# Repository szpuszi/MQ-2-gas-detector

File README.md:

# MQ-2 Gas Detector V1.0
It's my first custom PCB project created as part of the Hack Club Fallout.
It is designed to detect gas leaks and potential fire hazards.
This project also contains a case.

I made this because I wanted to practice making PCBs and create a practical safety device.
I use it by letting it sit and monitor gas levels in my room to ensure I'm in a safe environment.

## How it works:
The heart of this project is ATmega328P microcontroller. The board is powered via 5V USB-C (Adafruit 4090). The firmware features pre-heating phase (5mins) and a startup test function which lights up the LEDs and beeps the buzzer so you can know if it works correctly. It monitors gas levels in the air using an MQ-2 sensor and indicates safety levels by 3 LEDs and a buzzer:
- 🟢 Air is safe.
- 🟡 Gas levels are elevated. (warning)
- 🔴 High gas levels, it may be unsafe to inhale them.
<small> Thresholds were calibrated based on local home testing, sensitivity can vary depending on environment and gas type. </small>

### Shopping list 🛒: 
<small> BOM is available [here](Manufacturing/BOM.csv) </small>
You will also need:
- basic soldering kit (soldering iron, solder)
- PCB (can order on websites like JLCPCB, files for them are in Manufacturing Files.zip folder)
- Double Sided Tape
- DuPont Male/Female wires
- Glue (for the case, it needs to stick to plastic)
- cutting pliers

Total for everything is ≈ 40USD

### Manufacturing Notes🏭:
<small> All files required for production are included [here](Manufacturing/Manufacturing%20Files.zip) </small>

## 📖 Fallout Zine Page

# Assembly and firmware
Refer to the schematic and PCB layout for assembly. The PCB features a well detailed silkscreen with all components values and identifiers clearly marked to ensure easy and error-free assembly. The firmware is available [here](firmware/gas_detector.ino)
# Gallery📷
**CASE**

**PCB**

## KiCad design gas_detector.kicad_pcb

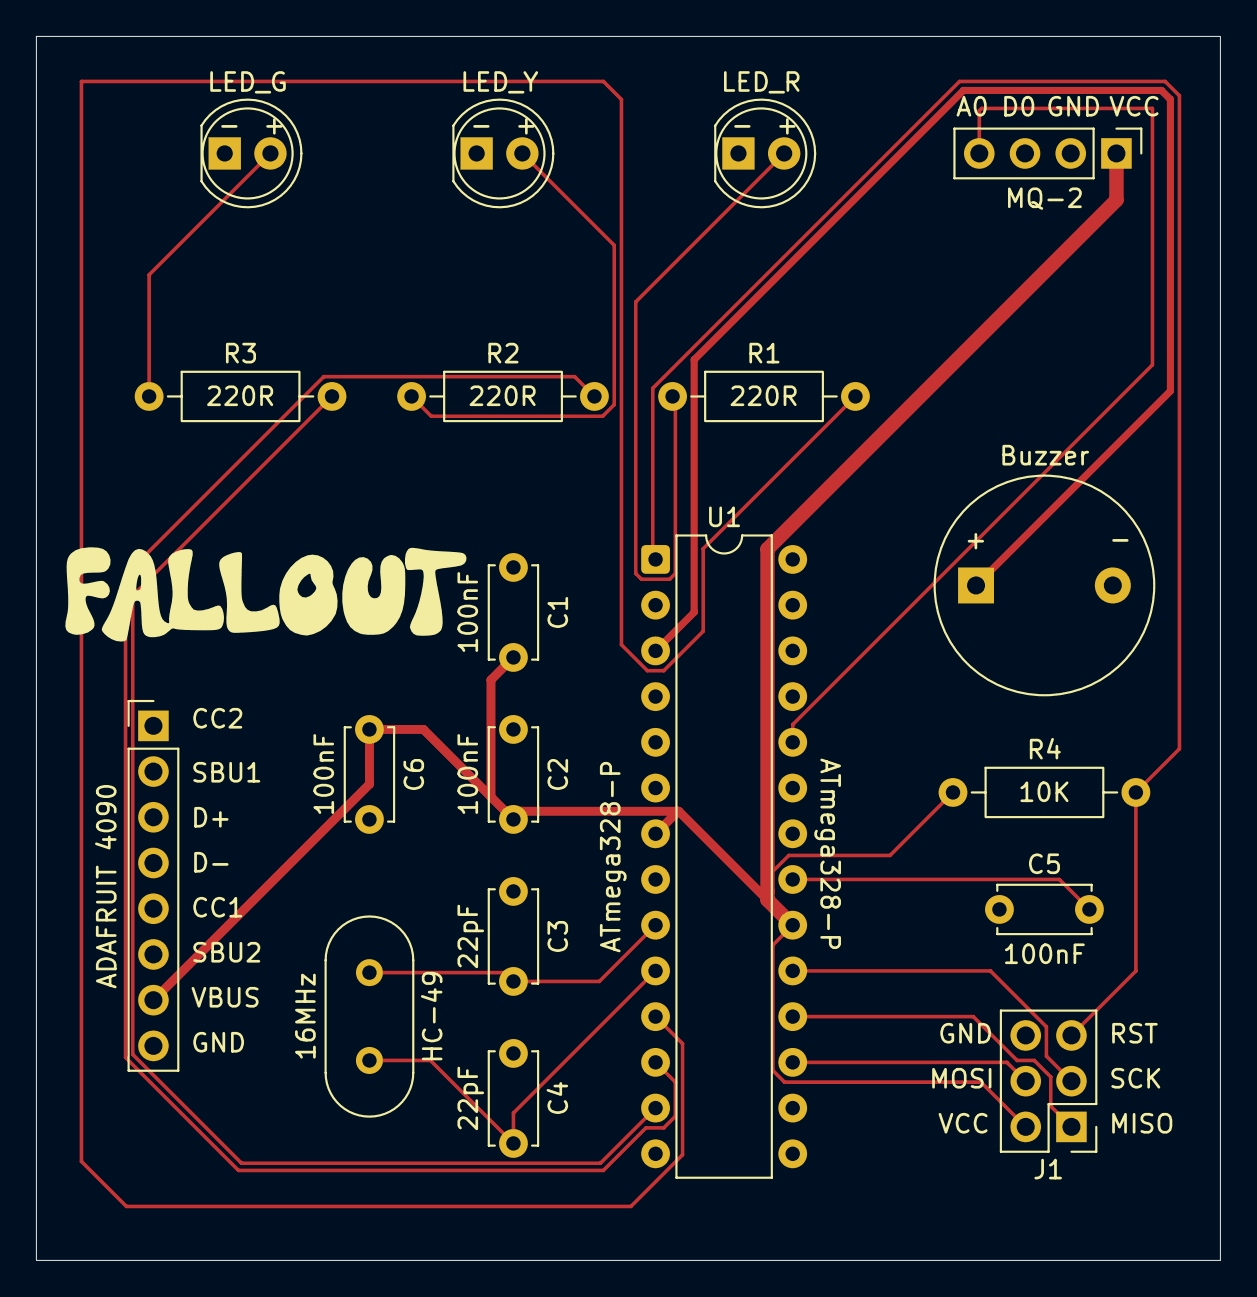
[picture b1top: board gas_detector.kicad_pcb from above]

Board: 2 copper layers, 65.8 x 68.0 mm, 19 parts (0 on the bottom side), 17 nets.

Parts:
Buzzer: Buzzer; Buzzer_12x9.5RM7.6
C1, C2, C5, C6: 100nF; C_Disc_D5.0mm_W2.5mm_P5.00mm
C3, C4: 22pF; C_Disc_D5.0mm_W2.5mm_P5.00mm
HC-49: 16MHz; Crystal_HC49-U_Vertical
J1: ISP; PinHeader_2x03_P2.54mm_Vertical
J2: Conn_01x08; PinHeader_1x08_P2.54mm_Vertical
LED_G: LED_G; LED_D5.0mm
LED_R: LED_R; LED_D5.0mm
LED_Y: LED_Y; LED_D5.0mm
MQ-2: MQ-2; PinHeader_1x04_P2.54mm_Vertical
R1, R2, R3: 220R; R_Axial_DIN0207_L6.3mm_D2.5mm_P10.16mm_Horizontal
R4: 10K; R_Axial_DIN0207_L6.3mm_D2.5mm_P10.16mm_Horizontal
U1: ATmega328P-P; DIP-28_W7.62mm

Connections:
GND: Buzzer.2 (-), C1.1, C2.1, C3.1, C4.1, C5.1, C6.1, J1.6 (GND), J2.8 (GND), LED_G.1 (K), LED_R.1 (K), LED_Y.1 (K), MQ-2.2 (GND), U1.8 (GND), U1.22 (GND)
unnamed: Buzzer.1 (+), U1.3 (PD1)
unnamed: LED_G.2 (A), R3.1
unnamed: LED_Y.2 (A), R2.1
unnamed: LED_R.2 (A), R1.1
unnamed: J1.1 (MISO), U1.18 (PB4)
unnamed: J1.4 (MOSI), U1.17 (PB3)
unnamed: J1.5 (RST), R4.2, U1.1 (~RESET/PC6)
unnamed: J1.3 (SCK), U1.19 (PB5)
unnamed: MQ-2.4 (A0), U1.24 (PC1)
unnamed: C5.2, U1.21 (AREF)
unnamed: R1.2, U1.11 (PD5)
unnamed: R2.2, U1.12 (PD6)
unnamed: R3.2, U1.13 (PD7)
unnamed: C3.2, HC-49.1, U1.9 (XTAL1/PB6)
unnamed: C4.2, HC-49.2, U1.10 (XTAL2/PB7)
VCC: C1.2, C2.2, C6.2, J1.2 (VCC), J2.7 (VBUS), MQ-2.1 (VCC), R4.1, U1.7 (VCC), U1.20 (AVCC)

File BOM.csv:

Designator,Value,Quantity,Description,Link
U1,ATmega328P-P,1,Microcontroller (DIP-28),https://www.digikey.com/en/products/detail/microchip-technol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
MQ-2,MQ-2,1,Gas Sensor Module,https://www.digikey.com/en/products/detail/olimex-ltd/SNS-MQ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
J2,Conn_01x08,1,USB Type C Breakout Board - Downstream Connection,https://www.adafruit.com/product/4090
R1-R3,220R,3,Resistor for LEDs (Through-hole),https://www.adafruit.com/product/2780
R4,10K,1,Pull-up Resistor (Through-hole),https://www.adafruit.com/product/2784
"C1,C2,C5,C6",100nF,4,Ceramic Capacitor,https://www.adafruit.com/product/753
"C3,C4",22pF,2,Ceramic Capacitor for Crystal,https://www.digikey.com/en/products/detail/vishay-beyschlag-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
Y1,16MHz,1,HC-49 Crystal,https://www.adafruit.com/product/2215
"D1,D2,D3","LED_G,LED_Y,LED_R",1,"G,Y,R LED",https://www.adafruit.com/product/4203
BZ1,Buzzer,1,12x9.5mm Active Buzzer (RM.7.5),https://www.amazon.com/dp/B0F1KCZGZG/ref=twister_B0FP83KQTB?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
J1,ISP,1,ISP programming interface,https://www.adafruit.com/product/2822
none,none,1,MQ-2 sensor female header,https://www.digikey.com/en/products/detail/samtec-inc/ESQT-1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
none,none,1,USBasp with 10-pin to 6-pin adapter,https://www.amazon.com/Geekstory-Microcontroller-Programmer-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

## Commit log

2026-04-18 Update README with project overview and details
    Added project details, shopping list, and manufacturing notes.
2026-04-18 Add KiCad files and Manufacturing Files
2026-04-18 Add firmware code
2026-04-18 Update tutorial section title in README
2026-04-18 Update README formatting and section headings
2026-04-18 Update README to refine components list
    Removed unnecessary items from the components list.
2026-04-18 Add BOM
2026-04-18 Rename BOM - BOM.csv to BOM.csv
2026-04-18 Fix formatting and descriptions in BOM.csv
    Updated BOM.csv to correct formatting and descriptions.
2026-04-18 Add USBasp to components list in README
    Added USBasp to the list of required components.
2026-04-18 Revise BOM.csv with updated components
    Updated BOM.csv to include new components and correct existing entries.
2026-04-18 Add STEP file
2026-04-18 Rename THE GAS DETECTOR.png to zine_page.png
2026-04-19 zine_page.png
2026-04-19 Rename THE GAS DETECTOR(1).png to zine_page.png
2026-04-19 Rename zine_page.png to images/zine_page.png
2026-04-19 Rename gas_detector.ino to firmware/gas_detector.ino
2026-04-19 Rename gas_detector.kicad_pcb to kicad files/gas_detector.kicad_pcb
2026-04-19 Rename gas_detector.kicad_prl to kicad files/gas_detector.kicad_prl
2026-04-19 Rename gas_detector.kicad_pro to kicad files/gas_detector.kicad_pro
2026-04-19 Rename gas_detector.kicad_sch to kicad filesgas_detector.kicad_sch
2026-04-19 Rename kicad filesgas_detector.kicad_sch to kicad files/gas_detector.kicad_sch
2026-04-19 Rename .step to gas detector.step
2026-04-19 Rename Manufacturing Files.zip to Manufacturing/Manufacturing Files.zip
2026-04-19 Rename BOM.csv to Manufacturing/BOM.csv
2026-04-19 Update links in README for BOM and manufacturing files
2026-04-19 Rename gas_detector.kicad_pcb to gas_detector.kicad_pcb
2026-04-19 Rename gas_detector.kicad_prl to gas_detector.kicad_prl
2026-04-19 Rename gas_detector.kicad_pro to gas_detector.kicad_pro
2026-04-19 Rename gas_detector.kicad_sch to gas_detector.kicad_sch
2026-04-19 Rename gas detector.step to gas_detector.step
2026-04-19 Update baseline and setup sequence in gas_detector
    Adjusted baseline value and modified setup sequence for LEDs and buzzer.
2026-04-19 Create LICENSE
2026-04-19 Correct capitalization for 'Male Header' in README
2026-04-19 Add double sided tape to materials list
2026-04-19 Rename Gas detector Case bottom.stl to 3d_models/Gas detector Case bottom.stl
2026-04-19 Rename Gas detector case top.stl to 3d_models/Gas detector case top.stl
2026-04-19 Rename gas_detector.kicad_pcb to hardware/gas_detector.kicad_pcb
2026-04-19 Rename gas_detector.kicad_prl to hardware/gas_detector.kicad_prl
2026-04-19 Rename gas_detector.kicad_pro to hardware/gas_detector.kicad_pro
2026-04-19 Rename gas_detector.kicad_sch to hardware/gas_detector.kicad_sch
2026-04-19 Add pcb.step file
2026-04-19 Rename pcb.step to 3d_models/pcb.step
2026-04-19 Rename gas_detector.pdf to schematic.pdf
2026-04-19 Rename 3d_models/Gas detector Case bottom.stl to 3d_models/case/Gas detector Case bottom.stl
2026-04-19 Rename 3d_models/Gas detector case top.stl to 3d_models/case/Gas detector case top.stl
2026-04-20 Remove an image from the README
2026-04-20 Increase baseline value from 105 to 110
2026-04-20 Add comments for baseline and threshold testing
    Added comments for environmental testing reference.
2026-04-20 Update glue description in README
    Clarified glue description for case assembly.
2026-04-22 Rename zine_page(1).pdf to zine_page.pdf
2026-04-22 Update BOM.csv with new components and links
2026-04-22 Update README with total cost and manufacturing details
    Added total cost and manufacturing notes to README.
2026-04-22 Add wire cutters to materials list
2026-04-26 Enhance case link with additional URLs
    Updated links for the project case in the README.
2026-04-30 Rename Gas detector case top.stl to Gas detector.stl
2026-04-30 Rename Gas detector Case bottom.stl to Gas detector Case bottom.stl
2026-04-30 Rename Gas detector case top.stl to Gas detector case top.stl
